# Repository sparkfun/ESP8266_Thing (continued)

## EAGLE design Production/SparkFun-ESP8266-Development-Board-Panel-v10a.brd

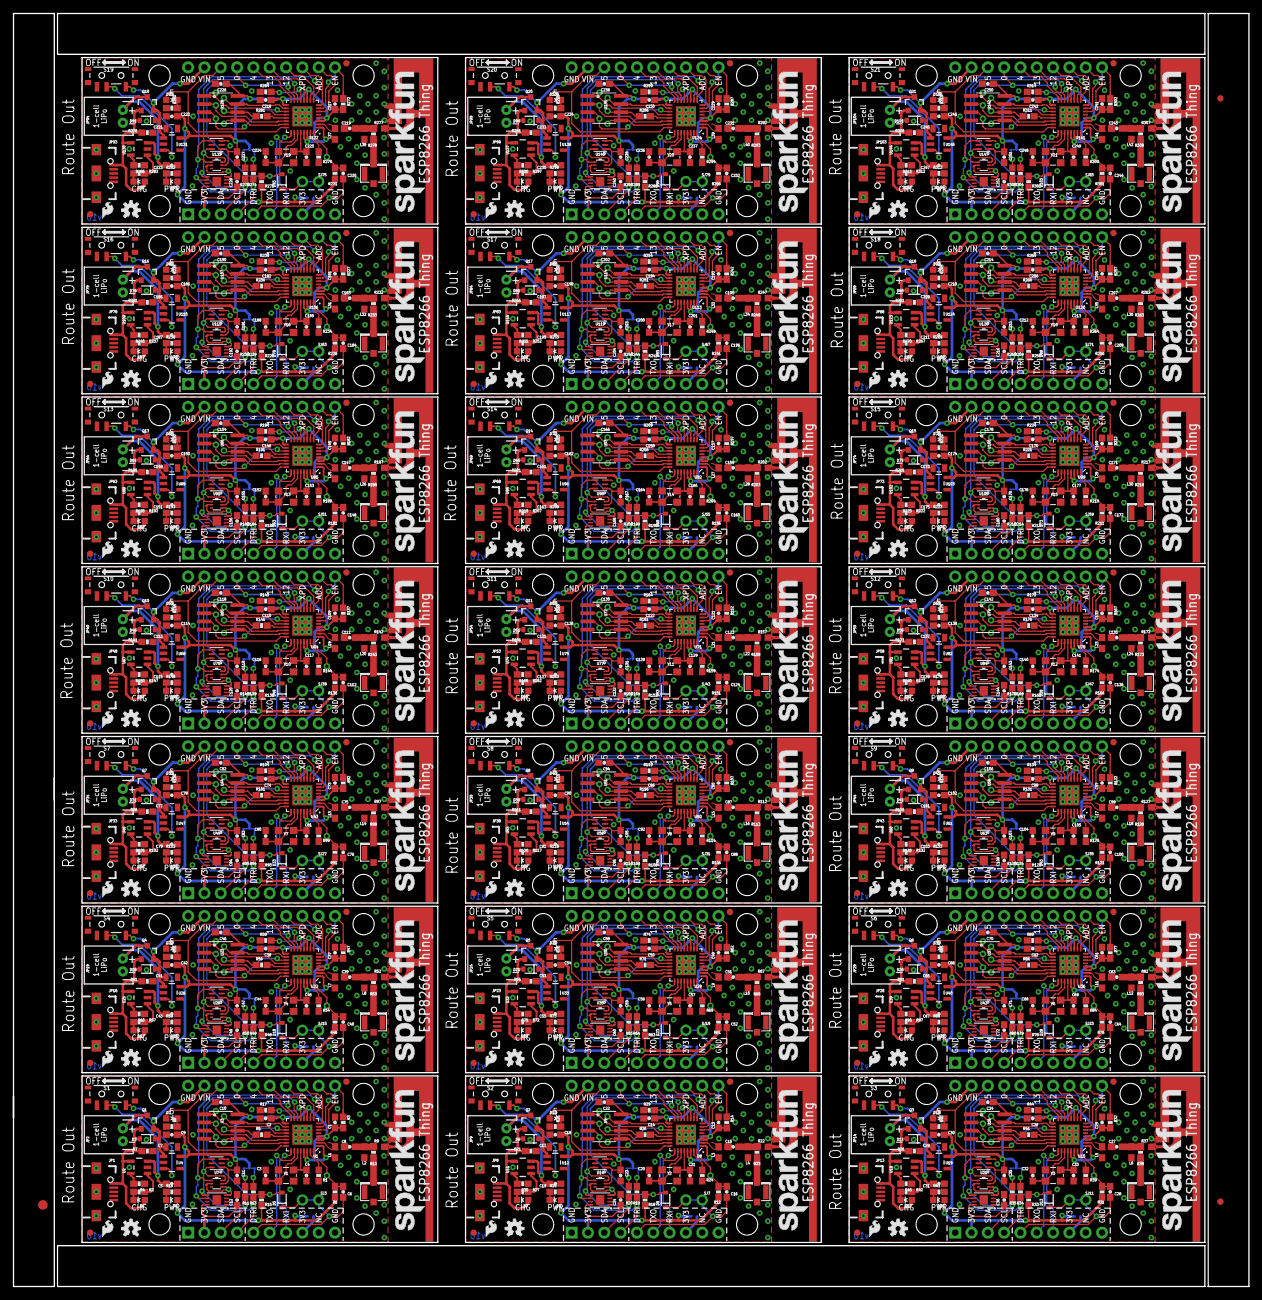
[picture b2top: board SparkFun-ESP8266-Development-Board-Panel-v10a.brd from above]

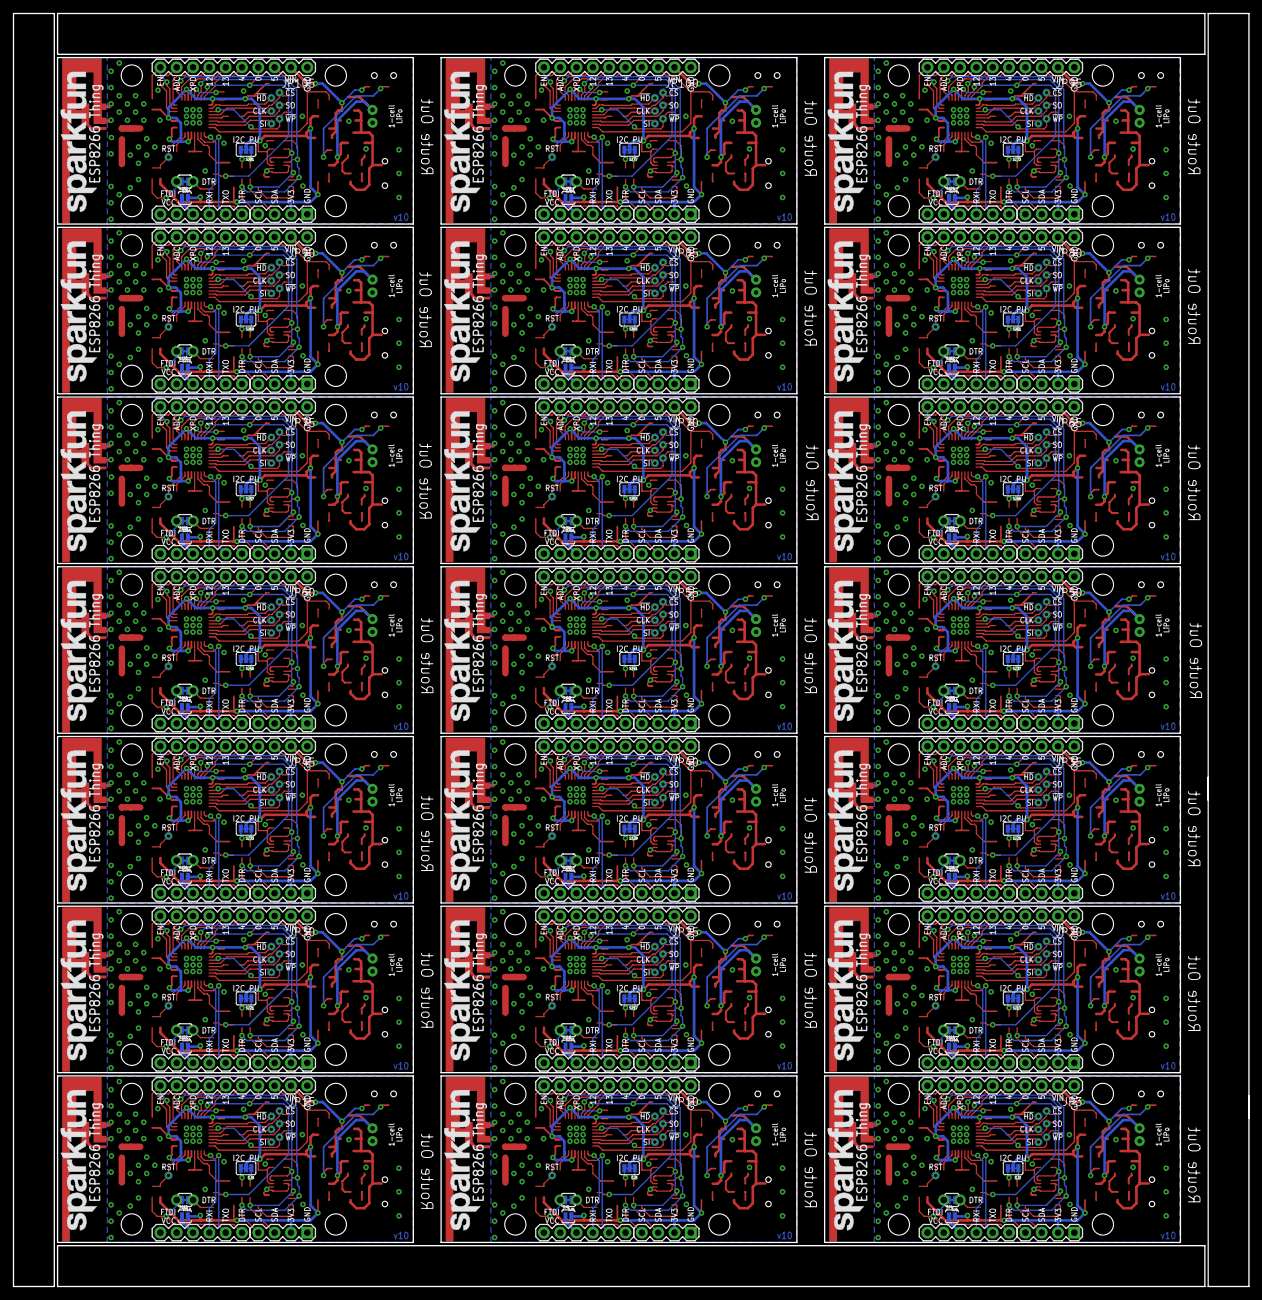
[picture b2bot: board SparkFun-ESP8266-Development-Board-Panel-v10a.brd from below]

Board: 2 copper layers, 192.3 x 198.1 mm, 1515 parts (294 on the bottom side), 924 nets.

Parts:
C1, C13, C25, C37, C49, C61, C73, C85, C97, C109, C121, C133, C145, C157, C169, C181, C193, C205, C217, C229, C241: 10uF; 0603-CAP
C2, C10, C11, C12, C14, C22, C23, C24, C26, C34, C35, C36, C38, C46, C47, C48, C50, C58, C59, C60, C62, C70, C71, C72, C74, C82, C83, C84, C86, C94, C95, C96, C98, C106, C107, C108, C110, C118, C119, C120, C122, C130, C131, C132, C134, C142, C143, C144, C146, C154, C155, C156, C158, C166, C167, C168, C170, C178, C179, C180, C182, C190, C191, C192, C194, C202, C203, C204, C206, C214, C215, C216, C218, C226, C227, C228, C230, C238, C239, C240, C242, C250, C251, C252: 0.1uF; 0603-CAP
C3, C4, C20, C21, C32, C33, C44, C45, C56, C57, C68, C69, C80, C81, C92, C93, C104, C105, C116, C117, C128, C129, C140, C141, C152, C153, C164, C165, C176, C177, C188, C189, C200, C201, C212, C213, C224, C225, C236, C237, C248, C249: 10pF; 0603-CAP
C5, C19, C31, C43, C55, C67, C79, C91, C103, C115, C127, C139, C151, C163, C175, C187, C199, C211, C223, C235, C247: 4.7uF; 0603-CAP
C6, C16, C28, C40, C52, C64, C76, C88, C100, C112, C124, C136, C148, C160, C172, C184, C196, C208, C220, C232, C244: 1.0uF; 0603-CAP
C7, C17, C29, C41, C53, C65, C77, C89, C101, C113, C125, C137, C149, C161, C173, C185, C197, C209, C221, C233, C245: 1.0uF; 0805
C8, C15, C27, C39, C51, C63, C75, C87, C99, C111, C123, C135, C147, C159, C171, C183, C195, C207, C219, C231, C243: 5.6pF; 0603-CAP
C9, C18, C30, C42, C54, C66, C78, C90, C102, C114, C126, C138, C150, C162, C174, C186, C198, C210, C222, C234, C246: 2.2uF; 0603-CAP
D1, D7, D12, D17, D22, D27, D32, D37, D42, D47, D52, D57, D62, D67, D72, D77, D82, D87, D92, D97, D102: YELLOW; LED-0603
D2, D10, D15, D20, D25, D30, D35, D40, D45, D50, D55, D60, D65, D70, D75, D80, D85, D90, D95, D100, D105: GREEN; LED-0603
D3, D6, D11, D16, D21, D26, D31, D36, D41, D46, D51, D56, D61, D66, D71, D76, D81, D86, D91, D96, D101: BAT20J; SOD-323
D4, D9, D14, D19, D24, D29, D34, D39, D44, D49, D54, D59, D64, D69, D74, D79, D84, D89, D94, D99, D104: RED; LED-0603
D5, D8, D13, D18, D23, D28, D33, D38, D43, D48, D53, D58, D63, D68, D73, D78, D83, D88, D93, D98, D103: SOD-323
E1, E2, E3, E4, E5, E6, E7, E8, E9, E10, E11, E12, E13, E14, E15, E16, E17, E18, E19, E20, E21: ANTENNATRACE; TRACE_ANTENNA_2.4GHZ_25.7MM
E$1: FIDUCIAL-1.5X3
E$5, E$6: FIDUCIAL-1X2
FID1, FID2, FID3, FID4, FID5, FID6, FID7, FID8, FID9, FID10, FID11, FID12, FID13, FID14, FID15, FID16, FID17, FID18, FID19, FID20, FID21, FID22, FID23, FID24, FID25, FID26, FID27, FID28, FID29, FID30, FID31, FID32, FID33, FID34, FID35, FID36, FID37, FID38, FID39, FID40, FID41, FID42: FIDUCIAL1X2; FIDUCIAL-1X2
J1, J2, J3, J4, J5, J6, J7, J8, J9, J10, J11, J12, J13, J14, J15, J16, J17, J18, J19, J20, J21: DNP; U.FL
JP1, JP8, JP13, JP18, JP23, JP28, JP33, JP38, JP43, JP48, JP53, JP58, JP63, JP68, JP73, JP78, JP83, JP88, JP93, JP98, JP103: USB; USB-B-MICRO-SMD_V03
JP2, JP9, JP14, JP19, JP24, JP29, JP34, JP39, JP44, JP49, JP54, JP59, JP64, JP69, JP74, JP79, JP84, JP89, JP94, JP99, JP104: LiPo; JST-2-PTH
JP3, JP10, JP15, JP20, JP25, JP30, JP35, JP40, JP45, JP50, JP55, JP60, JP65, JP70, JP75, JP80, JP85, JP90, JP95, JP100, JP105: M10"; 1X10
JP4, JP6, JP11, JP16, JP21, JP26, JP31, JP36, JP41, JP46, JP51, JP56, JP61, JP66, JP71, JP76, JP81, JP86, JP91, JP96, JP101: FTDI_BASICPTH; FTDI_BASIC
JP5, JP7, JP12, JP17, JP22, JP27, JP32, JP37, JP42, JP47, JP52, JP57, JP62, JP67, JP72, JP77, JP82, JP87, JP92, JP97, JP102: I2C; 1X04
L1, L2, L3, L4, L5, L6, L7, L8, L9, L10, L11, L12, L13, L14, L15, L16, L17, L18, L19, L20, L21, L22, L23, L24, L25, L26, L27, L28, L29, L30, L31, L32, L33, L34, L35, L36, L37, L38, L39, L40, L41, L42: DNP; 0603
LOGO1, LOGO2, LOGO5, LOGO8, LOGO9, LOGO12, LOGO13, LOGO16, LOGO17, LOGO20, LOGO21, LOGO24, LOGO25, LOGO28, LOGO29, LOGO32, LOGO33, LOGO36, LOGO37, LOGO40, LOGO41, LOGO44, LOGO45, LOGO48, LOGO49, LOGO52, LOGO53, LOGO56, LOGO57, LOGO60, LOGO61, LOGO64, LOGO65, LOGO68, LOGO69, LOGO72, LOGO73, LOGO76, LOGO77, LOGO80, LOGO81, LOGO84: SFE_LOGO_NAME.2_INCH; SFE_LOGO_NAME_.2
LOGO3, LOGO6, LOGO10, LOGO14, LOGO18, LOGO22, LOGO26, LOGO30, LOGO34, LOGO38, LOGO42, LOGO46, LOGO50, LOGO54, LOGO58, LOGO62, LOGO66, LOGO70, LOGO74, LOGO78, LOGO82: SFE_LOGO_FLAME.1_INCH; SFE_LOGO_FLAME_.1
LOGO4, LOGO7, LOGO11, LOGO15, LOGO19, LOGO23, LOGO27, LOGO31, LOGO35, LOGO39, LOGO43, LOGO47, LOGO51, LOGO55, LOGO59, LOGO63, LOGO67, LOGO71, LOGO75, LOGO79, LOGO83: OSHW-LOGOS; OSHW-LOGO-S
Q1, Q2, Q3, Q4, Q5, Q6, Q7, Q8, Q9, Q10, Q11, Q12, Q13, Q14, Q15, Q16, Q17, Q18, Q19, Q20, Q21: 2.5A/30V; SOT23-3
R1, R24, R39, R54, R69, R84, R99, R114, R129, R144, R159, R174, R189, R204, R219, R234, R249, R264, R279, R294, R309: 12k; 0603-RES
R2, R5, R8, R16, R25, R26, R27, R28, R40, R41, R42, R43, R55, R56, R57, R58, R70, R71, R72, R73, R85, R86, R87, R88, R100, R101, R102, R103, R115, R116, R117, R118, R130, R131, R132, R133, R145, R146, R147, R148, R160, R161, R162, R163, R175, R176, R177, R178, R190, R191, R192, R193, R205, R206, R207, R208, R220, R221, R222, R223, R235, R236, R237, R238, R250, R251, R252, R253, R265, R266, R267, R268, R280, R281, R282, R283, R295, R296, R297, R298, R310, R311, R312, R313: 200; 0603-RES
R3, R6, R7, R12, R14, R17, R21, R29, R31, R32, R36, R44, R46, R47, R51, R59, R61, R62, R66, R74, R76, R77, R81, R89, R91, R92, R96, R104, R106, R107, R111, R119, R121, R122, R126, R134, R136, R137, R141, R149, R151, R152, R156, R164, R166, R167, R171, R179, R181, R182, R186, R194, R196, R197, R201, R209, R211, R212, R216, R224, R226, R227, R231, R239, R241, R242, R246, R254, R256, R257, R261, R269, R271, R272, R276, R284, R286, R287, R291, R299, R301, R302, R306, R314: 10K; 0603-RES
R4, R30, R45, R60, R75, R90, R105, R120, R135, R150, R165, R180, R195, R210, R225, R240, R255, R270, R285, R300, R315: 2.0k; 0603-RES
R9, R22, R37, R52, R67, R82, R97, R112, R127, R142, R157, R172, R187, R202, R217, R232, R247, R262, R277, R292, R307: 0; 0603
R10, R23, R38, R53, R68, R83, R98, R113, R128, R143, R158, R173, R188, R203, R218, R233, R248, R263, R278, R293, R308: DNP; 0603-RES
R11, R13, R19, R20, R34, R35, R49, R50, R64, R65, R79, R80, R94, R95, R109, R110, R124, R125, R139, R140, R154, R155, R169, R170, R184, R185, R199, R200, R214, R215, R229, R230, R244, R245, R259, R260, R274, R275, R289, R290, R304, R305: 2.2k; 0603-RES
R15, R18, R33, R48, R63, R78, R93, R108, R123, R138, R153, R168, R183, R198, R213, R228, R243, R258, R273, R288, R303: 1K; 0603-RES
S1, S2, S3, S4, S5, S6, S7, S8, S9, S10, S11, S12, S13, S14, S15, S16, S17, S18, S19, S20, S21: SWITCH-SPST-SMD-A
SJ1, SJ8, SJ12, SJ16, SJ20, SJ24, SJ28, SJ32, SJ36, SJ40, SJ44, SJ48, SJ52, SJ56, SJ60, SJ64, SJ68, SJ72, SJ76, SJ80, SJ84: PAD-JUMPER-2-NC_BY_TRACE_YES_SILK
SJ2, SJ5, SJ9, SJ13, SJ17, SJ21, SJ25, SJ29, SJ33, SJ37, SJ41, SJ45, SJ49, SJ53, SJ57, SJ61, SJ65, SJ69, SJ73, SJ77, SJ81: PAD-JUMPER-3-3OF3_NC_BY_TRACE_YES_SILK_FULL_BOX
SJ3, SJ7, SJ11, SJ15, SJ19, SJ23, SJ27, SJ31, SJ35, SJ39, SJ43, SJ47, SJ51, SJ55, SJ59, SJ63, SJ67, SJ71, SJ75, SJ79, SJ83: PTH-JUMPER-NC_BOTTOM_NO_SILK
SJ4, SJ6, SJ10, SJ14, SJ18, SJ22, SJ26, SJ30, SJ34, SJ38, SJ42, SJ46, SJ50, SJ54, SJ58, SJ62, SJ66, SJ70, SJ74, SJ78, SJ82: PAD-JUMPER-2-NO_YES_SILK
STANDOFF1, STANDOFF2, STANDOFF3, STANDOFF4, STANDOFF5, STANDOFF6, STANDOFF7, STANDOFF8, STANDOFF9, STANDOFF10, STANDOFF11, STANDOFF12, STANDOFF13, STANDOFF14, STANDOFF15, STANDOFF16, STANDOFF17, STANDOFF18, STANDOFF19, STANDOFF20, STANDOFF21, STANDOFF22, STANDOFF23, STANDOFF24, STANDOFF25, STANDOFF26, STANDOFF27, STANDOFF28, STANDOFF29, STANDOFF30, STANDOFF31, STANDOFF32, STANDOFF33, STANDOFF34, STANDOFF35, STANDOFF36, STANDOFF37, STANDOFF38, STANDOFF39, STANDOFF40, STANDOFF41, STANDOFF42, STANDOFF43, STANDOFF44, STANDOFF45, STANDOFF46, STANDOFF47, STANDOFF48, STANDOFF49, STANDOFF50, STANDOFF51, STANDOFF52, STANDOFF53, STANDOFF54, STANDOFF55, STANDOFF56, STANDOFF57, STANDOFF58, STANDOFF59, STANDOFF60, STANDOFF61, STANDOFF62, STANDOFF63, STANDOFF64, STANDOFF65, STANDOFF66, STANDOFF67, STANDOFF68, STANDOFF69, STANDOFF70, STANDOFF71, STANDOFF72, STANDOFF73, STANDOFF74, STANDOFF75, STANDOFF76, STANDOFF77, STANDOFF78, STANDOFF79, STANDOFF80, STANDOFF81, STANDOFF82, STANDOFF83, STANDOFF84: STAND-OFF
TP1, TP2, TP3, TP4, TP5, TP6, TP7, TP8, TP9, TP10, TP11, TP12, TP13, TP14, TP15, TP16, TP17, TP18, TP19, TP20, TP21, TP22, TP23, TP24, TP25, TP26, TP27, TP28, TP29, TP30, TP31, TP32, TP33, TP34, TP35, TP36, TP37, TP38, TP39, TP40, TP41, TP42, TP43, TP44, TP45, TP46, TP47, TP48, TP49, TP50, TP51, TP52, TP53, TP54, TP55, TP56, TP57, TP58, TP59, TP60, TP61, TP62, TP63, TP64, TP65, TP66, TP67, TP68, TP69, TP70, TP71, TP72, TP73, TP74, TP75, TP76, TP77, TP78, TP79, TP80, TP81, TP82, TP83, TP84, TP85, TP86, TP87, TP88, TP89, TP90, TP91, TP92, TP93, TP94, TP95, TP96, TP97, TP98, TP99, TP100, TP101, TP102, TP103, TP104, TP105, TP106, TP107, TP108, TP109, TP110, TP111, TP112, TP113, TP114, TP115, TP116, TP117, TP118, TP119, TP120, TP121, TP122, TP123, TP124, TP125, TP126, TP127, TP128, TP129, TP130, TP131, TP132, TP133, TP134, TP135, TP136, TP137, TP138, TP139, TP140, TP141, TP142, TP143, TP144, TP145, TP146, TP147: PAD.03X.05
U1, U8, U15, U22, U29, U36, U43, U50, U57, U64, U71, U78, U85, U92, U99, U106, U113, U120, U127, U134, U141: ESP8266; QFN32
U2, U11, U18, U25, U32, U39, U46, U53, U60, U67, U74, U81, U88, U95, U102, U109, U116, U123, U130, U137, U144: MCP73831; SOT23-5
U3, U9, U16, U23, U30, U37, U44, U51, U58, U65, U72, U79, U86, U93, U100, U107, U114, U121, U128, U135, U142: AT25SF041-SOIC8; SO08
U4, U12, U19, U26, U33, U40, U47, U54, U61, U68, U75, U82, U89, U96, U103, U110, U117, U124, U131, U138, U145: AP2112K-3.3V; SOT23-5
U5, U10, U17, U24, U31, U38, U45, U52, U59, U66, U73, U80, U87, U94, U101, U108, U115, U122, U129, U136, U143: ATECC108-MAHDA; UDFN8
U6, U13, U20, U27, U34, U41, U48, U55, U62, U69, U76, U83, U90, U97, U104, U111, U118, U125, U132, U139, U146: TMP1021:1; SOT563-2
U7, U14, U21, U28, U35, U42, U49, U56, U63, U70, U77, U84, U91, U98, U105, U112, U119, U126, U133, U140, U147: TSL2561FN; FN-6
Y1, Y2, Y3, Y4, Y5, Y6, Y7, Y8, Y9, Y10, Y11, Y12, Y13, Y14, Y15, Y16, Y17, Y18, Y19, Y20, Y21: 26MHz; CRYSTAL-SMD-3.2X2.5

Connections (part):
ADC: JP3.9, U1.6
ADC1: JP10.9, U8.6
ADC2: JP15.9, U15.6
ADC3: JP20.9, U22.6
ADC4: JP25.9, U29.6
ADC5: JP30.9, U36.6
ADC6: JP35.9, U43.6
ADC7: JP40.9, U50.6
ADC8: JP45.9, U57.6
ADC9: JP50.9, U64.6
ADC10: JP55.9, U71.6
ADC11: JP60.9, U78.6
ADC12: JP65.9, U85.6
ADC13: JP70.9, U92.6
ADC14: JP75.9, U99.6
ADC15: JP80.9, U106.6
ADC16: JP85.9, U113.6
ADC17: JP90.9, U120.6
ADC18: JP95.9, U127.6
ADC19: JP100.9, U134.6
ADC20: JP105.9, U141.6
ANT: J1.P$3, R10.1
ANT1: J2.P$3, R23.1
ANT2: J3.P$3, R38.1
ANT3: J4.P$3, R53.1
ANT4: J5.P$3, R68.1
ANT5: J6.P$3, R83.1
ANT6: J7.P$3, R98.1
ANT7: J8.P$3, R113.1
ANT8: J9.P$3, R128.1
ANT9: J10.P$3, R143.1
ANT10: J11.P$3, R158.1
ANT11: J12.P$3, R173.1
ANT12: J13.P$3, R188.1
ANT13: J14.P$3, R203.1
ANT14: J15.P$3, R218.1
ANT15: J16.P$3, R233.1
ANT16: J17.P$3, R248.1
ANT17: J18.P$3, R263.1
ANT18: J19.P$3, R278.1
ANT19: J20.P$3, R293.1
ANT20: J21.P$3, R308.1
CHIP_EN: JP3.10, R3.1, U1.7
CHIP_EN1: JP10.10, R14.1, U8.7
CHIP_EN2: JP15.10, R32.1, U15.7
CHIP_EN3: JP20.10, R47.1, U22.7
CHIP_EN4: JP25.10, R62.1, U29.7
CHIP_EN5: JP30.10, R77.1, U36.7
CHIP_EN6: JP35.10, R92.1, U43.7
CHIP_EN7: JP40.10, R107.1, U50.7
CHIP_EN8: JP45.10, R122.1, U57.7
CHIP_EN9: JP50.10, R137.1, U64.7
CHIP_EN10: JP55.10, R152.1, U71.7
CHIP_EN11: JP60.10, R167.1, U78.7
CHIP_EN12: JP65.10, R182.1, U85.7
CHIP_EN13: JP70.10, R197.1, U92.7
CHIP_EN14: JP75.10, R212.1, U99.7
CHIP_EN15: JP80.10, R227.1, U106.7
CHIP_EN16: JP85.10, R242.1, U113.7
CHIP_EN17: JP90.10, R257.1, U120.7
CHIP_EN18: JP95.10, R272.1, U127.7
CHIP_EN19: JP100.10, R287.1, U134.7
CHIP_EN20: JP105.10, R302.1, U141.7
DTR: C6.2, JP4.DTR, SJ1.2, SJ3.1
DTR1: C16.2, JP6.DTR, SJ7.1, SJ8.2
DTR2: C28.2, JP11.DTR, SJ11.1, SJ12.2
DTR3: C40.2, JP16.DTR, SJ15.1, SJ16.2
DTR4: C52.2, JP21.DTR, SJ19.1, SJ20.2
DTR5: C64.2, JP26.DTR, SJ23.1, SJ24.2
DTR6: C76.2, JP31.DTR, SJ27.1, SJ28.2
DTR7: C88.2, JP36.DTR, SJ31.1, SJ32.2
DTR8: C100.2, JP41.DTR, SJ35.1, SJ36.2
DTR9: C112.2, JP46.DTR, SJ39.1, SJ40.2
DTR10: C124.2, JP51.DTR, SJ43.1, SJ44.2
DTR11: C136.2, JP56.DTR, SJ47.1, SJ48.2
DTR12: C148.2, JP61.DTR, SJ51.1, SJ52.2
DTR13: C160.2, JP66.DTR, SJ55.1, SJ56.2
DTR14: C172.2, JP71.DTR, SJ59.1, SJ60.2
DTR15: C184.2, JP76.DTR, SJ63.1, SJ64.2
DTR16: C196.2, JP81.DTR, SJ67.1, SJ68.2
DTR17: C208.2, JP86.DTR, SJ71.1, SJ72.2
DTR18: C220.2, JP91.DTR, SJ75.1, SJ76.2
DTR19: C232.2, JP96.DTR, SJ79.1, SJ80.2
DTR20: C244.2, JP101.DTR, SJ83.1, SJ84.2
FTDI_VCC: JP4.VCC, SJ4.1
FTDI_VCC1: JP6.VCC, SJ6.1
FTDI_VCC2: JP11.VCC, SJ10.1
FTDI_VCC3: JP16.VCC, SJ14.1
FTDI_VCC4: JP21.VCC, SJ18.1
FTDI_VCC5: JP26.VCC, SJ22.1
FTDI_VCC6: JP31.VCC, SJ26.1
FTDI_VCC7: JP36.VCC, SJ30.1
FTDI_VCC8: JP41.VCC, SJ34.1
FTDI_VCC9: JP46.VCC, SJ38.1
FTDI_VCC10: JP51.VCC, SJ42.1
FTDI_VCC11: JP56.VCC, SJ46.1
FTDI_VCC12: JP61.VCC, SJ50.1
FTDI_VCC13: JP66.VCC, SJ54.1
FTDI_VCC14: JP71.VCC, SJ58.1
FTDI_VCC15: JP76.VCC, SJ62.1
FTDI_VCC16: JP81.VCC, SJ66.1
FTDI_VCC17: JP86.VCC, SJ70.1
FTDI_VCC18: JP91.VCC, SJ74.1
FTDI_VCC19: JP96.VCC, SJ78.1
FTDI_VCC20: JP101.VCC, SJ82.1
GND: C1.2, C2.2, C3.1, C4.1, C5.2, C7.2, C9.2, C10.2, C11.2, C12.2, E1.GND, E1.GND2, J1.P$1, J1.P$2, JP1.GND1, JP1.SHIELD1, JP1.SHIELD2, JP1.SHIELD3, JP2.1, JP3.1, JP4.GND, JP5.1, L1.2, L2.2, R1.1, R4.1, R7.1, R8.2, R16.2, R17.1, S1.1, U1.EP, U2.2, U3.4, U4.2, U5.4, U6.2, U6.4, U7.2, U7.3, Y1.2, Y1.4
GND1: C13.2, C14.2, C17.2, C18.2, C19.2, C20.1, C21.1, C22.2, C23.2, C24.2, E2.GND, E2.GND2, J2.P$1, J2.P$2, JP6.GND, JP7.1, JP8.GND1, JP8.SHIELD1, JP8.SHIELD2, JP8.SHIELD3, JP9.1, JP10.1, L3.2, L4.2, R21.1, R24.1, R25.2, R28.2, R29.1, R30.1, S2.1, U8.EP, U9.4, U10.4, U11.2, U12.2, U13.2, U13.4, U14.2, U14.3, Y2.2, Y2.4
GND2: C25.2, C26.2, C29.2, C30.2, C31.2, C32.1, C33.1, C34.2, C35.2, C36.2, E3.GND, E3.GND2, J3.P$1, J3.P$2, JP11.GND, JP12.1, JP13.GND1, JP13.SHIELD1, JP13.SHIELD2, JP13.SHIELD3, JP14.1, JP15.1, L5.2, L6.2, R36.1, R39.1, R40.2, R43.2, R44.1, R45.1, S3.1, U15.EP, U16.4, U17.4, U18.2, U19.2, U20.2, U20.4, U21.2, U21.3, Y3.2, Y3.4
GND3: C37.2, C38.2, C41.2, C42.2, C43.2, C44.1, C45.1, C46.2, C47.2, C48.2, E4.GND, E4.GND2, J4.P$1, J4.P$2, JP16.GND, JP17.1, JP18.GND1, JP18.SHIELD1, JP18.SHIELD2, JP18.SHIELD3, JP19.1, JP20.1, L7.2, L8.2, R51.1, R54.1, R55.2, R58.2, R59.1, R60.1, S4.1, U22.EP, U23.4, U24.4, U25.2, U26.2, U27.2, U27.4, U28.2, U28.3, Y4.2, Y4.4
GND4: C49.2, C50.2, C53.2, C54.2, C55.2, C56.1, C57.1, C58.2, C59.2, C60.2, E5.GND, E5.GND2, J5.P$1, J5.P$2, JP21.GND, JP22.1, JP23.GND1, JP23.SHIELD1, JP23.SHIELD2, JP23.SHIELD3, JP24.1, JP25.1, L9.2, L10.2, R66.1, R69.1, R70.2, R73.2, R74.1, R75.1, S5.1, U29.EP, U30.4, U31.4, U32.2, U33.2, U34.2, U34.4, U35.2, U35.3, Y5.2, Y5.4
GND5: C61.2, C62.2, C65.2, C66.2, C67.2, C68.1, C69.1, C70.2, C71.2, C72.2, E6.GND, E6.GND2, J6.P$1, J6.P$2, JP26.GND, JP27.1, JP28.GND1, JP28.SHIELD1, JP28.SHIELD2, JP28.SHIELD3, JP29.1, JP30.1, L11.2, L12.2, R81.1, R84.1, R85.2, R88.2, R89.1, R90.1, S6.1, U36.EP, U37.4, U38.4, U39.2, U40.2, U41.2, U41.4, U42.2, U42.3, Y6.2, Y6.4
GND6: C73.2, C74.2, C77.2, C78.2, C79.2, C80.1, C81.1, C82.2, C83.2, C84.2, E7.GND, E7.GND2, J7.P$1, J7.P$2, JP31.GND, JP32.1, JP33.GND1, JP33.SHIELD1, JP33.SHIELD2, JP33.SHIELD3, JP34.1, JP35.1, L13.2, L14.2, R96.1, R99.1, R100.2, R103.2, R104.1, R105.1, S7.1, U43.EP, U44.4, U45.4, U46.2, U47.2, U48.2, U48.4, U49.2, U49.3, Y7.2, Y7.4
GND7: C85.2, C86.2, C89.2, C90.2, C91.2, C92.1, C93.1, C94.2, C95.2, C96.2, E8.GND, E8.GND2, J8.P$1, J8.P$2, JP36.GND, JP37.1, JP38.GND1, JP38.SHIELD1, JP38.SHIELD2, JP38.SHIELD3, JP39.1, JP40.1, L15.2, L16.2, R111.1, R114.1, R115.2, R118.2, R119.1, R120.1, S8.1, U50.EP, U51.4, U52.4, U53.2, U54.2, U55.2, U55.4, U56.2, U56.3, Y8.2, Y8.4
GND8: C97.2, C98.2, C101.2, C102.2, C103.2, C104.1, C105.1, C106.2, C107.2, C108.2, E9.GND, E9.GND2, J9.P$1, J9.P$2, JP41.GND, JP42.1, JP43.GND1, JP43.SHIELD1, JP43.SHIELD2, JP43.SHIELD3, JP44.1, JP45.1, L17.2, L18.2, R126.1, R129.1, R130.2, R133.2, R134.1, R135.1, S9.1, U57.EP, U58.4, U59.4, U60.2, U61.2, U62.2, U62.4, U63.2, U63.3, Y9.2, Y9.4
GND9: C109.2, C110.2, C113.2, C114.2, C115.2, C116.1, C117.1, C118.2, C119.2, C120.2, E10.GND, E10.GND2, J10.P$1, J10.P$2, JP46.GND, JP47.1, JP48.GND1, JP48.SHIELD1, JP48.SHIELD2, JP48.SHIELD3, JP49.1, JP50.1, L19.2, L20.2, R141.1, R144.1, R145.2, R148.2, R149.1, R150.1, S10.1, U64.EP, U65.4, U66.4, U67.2, U68.2, U69.2, U69.4, U70.2, U70.3, Y10.2, Y10.4
GND10: C121.2, C122.2, C125.2, C126.2, C127.2, C128.1, C129.1, C130.2, C131.2, C132.2, E11.GND, E11.GND2, J11.P$1, J11.P$2, JP51.GND, JP52.1, JP53.GND1, JP53.SHIELD1, JP53.SHIELD2, JP53.SHIELD3, JP54.1, JP55.1, L21.2, L22.2, R156.1, R159.1, R160.2, R163.2, R164.1, R165.1, S11.1, U71.EP, U72.4, U73.4, U74.2, U75.2, U76.2, U76.4, U77.2, U77.3, Y11.2, Y11.4
GND11: C133.2, C134.2, C137.2, C138.2, C139.2, C140.1, C141.1, C142.2, C143.2, C144.2, E12.GND, E12.GND2, J12.P$1, J12.P$2, JP56.GND, JP57.1, JP58.GND1, JP58.SHIELD1, JP58.SHIELD2, JP58.SHIELD3, JP59.1, JP60.1, L23.2, L24.2, R171.1, R174.1, R175.2, R178.2, R179.1, R180.1, S12.1, U78.EP, U79.4, U80.4, U81.2, U82.2, U83.2, U83.4, U84.2, U84.3, Y12.2, Y12.4
GND12: C145.2, C146.2, C149.2, C150.2, C151.2, C152.1, C153.1, C154.2, C155.2, C156.2, E13.GND, E13.GND2, J13.P$1, J13.P$2, JP61.GND, JP62.1, JP63.GND1, JP63.SHIELD1, JP63.SHIELD2, JP63.SHIELD3, JP64.1, JP65.1, L25.2, L26.2, R186.1, R189.1, R190.2, R193.2, R194.1, R195.1, S13.1, U85.EP, U86.4, U87.4, U88.2, U89.2, U90.2, U90.4, U91.2, U91.3, Y13.2, Y13.4
GND13: C157.2, C158.2, C161.2, C162.2, C163.2, C164.1, C165.1, C166.2, C167.2, C168.2, E14.GND, E14.GND2, J14.P$1, J14.P$2, JP66.GND, JP67.1, JP68.GND1, JP68.SHIELD1, JP68.SHIELD2, JP68.SHIELD3, JP69.1, JP70.1, L27.2, L28.2, R201.1, R204.1, R205.2, R208.2, R209.1, R210.1, S14.1, U92.EP, U93.4, U94.4, U95.2, U96.2, U97.2, U97.4, U98.2, U98.3, Y14.2, Y14.4
GND14: C169.2, C170.2, C173.2, C174.2, C175.2, C176.1, C177.1, C178.2, C179.2, C180.2, E15.GND, E15.GND2, J15.P$1, J15.P$2, JP71.GND, JP72.1, JP73.GND1, JP73.SHIELD1, JP73.SHIELD2, JP73.SHIELD3, JP74.1, JP75.1, L29.2, L30.2, R216.1, R219.1, R220.2, R223.2, R224.1, R225.1, S15.1, U99.EP, U100.4, U101.4, U102.2, U103.2, U104.2, U104.4, U105.2, U105.3, Y15.2, Y15.4
GND15: C181.2, C182.2, C185.2, C186.2, C187.2, C188.1, C189.1, C190.2, C191.2, C192.2, E16.GND, E16.GND2, J16.P$1, J16.P$2, JP76.GND, JP77.1, JP78.GND1, JP78.SHIELD1, JP78.SHIELD2, JP78.SHIELD3, JP79.1, JP80.1, L31.2, L32.2, R231.1, R234.1, R235.2, R238.2, R239.1, R240.1, S16.1, U106.EP, U107.4, U108.4, U109.2, U110.2, U111.2, U111.4, U112.2, U112.3, Y16.2, Y16.4
GND16: C193.2, C194.2, C197.2, C198.2, C199.2, C200.1, C201.1, C202.2, C203.2, C204.2, E17.GND, E17.GND2, J17.P$1, J17.P$2, JP81.GND, JP82.1, JP83.GND1, JP83.SHIELD1, JP83.SHIELD2, JP83.SHIELD3, JP84.1, JP85.1, L33.2, L34.2, R246.1, R249.1, R250.2, R253.2, R254.1, R255.1, S17.1, U113.EP, U114.4, U115.4, U116.2, U117.2, U118.2, U118.4, U119.2, U119.3, Y17.2, Y17.4
GND17: C205.2, C206.2, C209.2, C210.2, C211.2, C212.1, C213.1, C214.2, C215.2, C216.2, E18.GND, E18.GND2, J18.P$1, J18.P$2, JP86.GND, JP87.1, JP88.GND1, JP88.SHIELD1, JP88.SHIELD2, JP88.SHIELD3, JP89.1, JP90.1, L35.2, L36.2, R261.1, R264.1, R265.2, R268.2, R269.1, R270.1, S18.1, U120.EP, U121.4, U122.4, U123.2, U124.2, U125.2, U125.4, U126.2, U126.3, Y18.2, Y18.4
GND18: C217.2, C218.2, C221.2, C222.2, C223.2, C224.1, C225.1, C226.2, C227.2, C228.2, E19.GND, E19.GND2, J19.P$1, J19.P$2, JP91.GND, JP92.1, JP93.GND1, JP93.SHIELD1, JP93.SHIELD2, JP93.SHIELD3, JP94.1, JP95.1, L37.2, L38.2, R276.1, R279.1, R280.2, R283.2, R284.1, R285.1, S19.1, U127.EP, U128.4, U129.4, U130.2, U131.2, U132.2, U132.4, U133.2, U133.3, Y19.2, Y19.4
GND19: C229.2, C230.2, C233.2, C234.2, C235.2, C236.1, C237.1, C238.2, C239.2, C240.2, E20.GND, E20.GND2, J20.P$1, J20.P$2, JP96.GND, JP97.1, JP98.GND1, JP98.SHIELD1, JP98.SHIELD2, JP98.SHIELD3, JP99.1, JP100.1, L39.2, L40.2, R291.1, R294.1, R295.2, R298.2, R299.1, R300.1, S20.1, U134.EP, U135.4, U136.4, U137.2, U138.2, U139.2, U139.4, U140.2, U140.3, Y20.2, Y20.4
GND20: C241.2, C242.2, C245.2, C246.2, C247.2, C248.1, C249.1, C250.2, C251.2, C252.2, E21.GND, E21.GND2, J21.P$1, J21.P$2, JP101.GND, JP102.1, JP103.GND1, JP103.SHIELD1, JP103.SHIELD2, JP103.SHIELD3, JP104.1, JP105.1, L41.2, L42.2, R306.1, R309.1, R310.2, R313.2, R314.1, R315.1, S21.1, U141.EP, U142.4, U143.4, U144.2, U145.2, U146.2, U146.4, U147.2, U147.3, Y21.2, Y21.4
GPIO0: D5.A, JP3.4, R15.1, U1.15
GPIO1: D8.A, JP10.4, R18.1, U8.15
GPIO2: D10.A, JP10.3, U8.24
GPIO2/SDA: JP5.3, R11.1, U1.14, U5.5, U6.6, U7.6
GPIO2/SDA1: JP7.3, R20.1, U8.14, U10.5, U13.6, U14.6
GPIO2/SDA2: JP12.3, R35.1, U15.14, U17.5, U20.6, U21.6
GPIO2/SDA3: JP17.3, R50.1, U22.14, U24.5, U27.6, U28.6
GPIO2/SDA4: JP22.3, R65.1, U29.14, U31.5, U34.6, U35.6
GPIO2/SDA5: JP27.3, R80.1, U36.14, U38.5, U41.6, U42.6
GPIO2/SDA6: JP32.3, R95.1, U43.14, U45.5, U48.6, U49.6
GPIO2/SDA7: JP37.3, R110.1, U50.14, U52.5, U55.6, U56.6
GPIO2/SDA8: JP42.3, R125.1, U57.14, U59.5, U62.6, U63.6
GPIO2/SDA9: JP47.3, R140.1, U64.14, U66.5, U69.6, U70.6
GPIO2/SDA10: JP52.3, R155.1, U71.14, U73.5, U76.6, U77.6
GPIO2/SDA11: JP57.3, R170.1, U78.14, U80.5, U83.6, U84.6
GPIO2/SDA12: JP62.3, R185.1, U85.14, U87.5, U90.6, U91.6
GPIO2/SDA13: JP67.3, R200.1, U92.14, U94.5, U97.6, U98.6
GPIO2/SDA14: JP72.3, R215.1, U99.14, U101.5, U104.6, U105.6
GPIO2/SDA15: JP77.3, R230.1, U106.14, U108.5, U111.6, U112.6
GPIO2/SDA16: JP82.3, R245.1, U113.14, U115.5, U118.6, U119.6
GPIO2/SDA17: JP87.3, R260.1, U120.14, U122.5, U125.6, U126.6
GPIO2/SDA18: JP92.3, R275.1, U127.14, U129.5, U132.6, U133.6
GPIO2/SDA19: JP97.3, R290.1, U134.14, U136.5, U139.6, U140.6
GPIO2/SDA20: JP102.3, R305.1, U141.14, U143.5, U146.6, U147.6
GPIO3: JP10.5, U8.16
GPIO4: JP3.5, U1.16
GPIO5: D2.A, JP3.3, U1.24
GPIO6: JP10.8, U8.8
GPIO7: R29.2, U8.13
GPIO8: JP10.6, U8.12
GPIO9: JP10.7, U8.10
GPIO10: D13.A, JP15.4, R33.1, U15.15
GPIO11: D15.A, JP15.3, U15.24
GPIO12: JP3.7, U1.10
GPIO13: JP3.6, U1.12
GPIO14: JP15.5, U15.16
GPIO14/SCL: JP5.4, R13.1, U1.9, U5.6, U6.1, U7.4
GPIO14/SCL1: JP7.4, R19.1, U8.9, U10.6, U13.1, U14.4
GPIO14/SCL2: JP12.4, R34.1, U15.9, U17.6, U20.1, U21.4
GPIO14/SCL3: JP17.4, R49.1, U22.9, U24.6, U27.1, U28.4
GPIO14/SCL4: JP22.4, R64.1, U29.9, U31.6, U34.1, U35.4
GPIO14/SCL5: JP27.4, R79.1, U36.9, U38.6, U41.1, U42.4
GPIO14/SCL6: JP32.4, R94.1, U43.9, U45.6, U48.1, U49.4
GPIO14/SCL7: JP37.4, R109.1, U50.9, U52.6, U55.1, U56.4
GPIO14/SCL8: JP42.4, R124.1, U57.9, U59.6, U62.1, U63.4
GPIO14/SCL9: JP47.4, R139.1, U64.9, U66.6, U69.1, U70.4
GPIO14/SCL10: JP52.4, R154.1, U71.9, U73.6, U76.1, U77.4
GPIO14/SCL11: JP57.4, R169.1, U78.9, U80.6, U83.1, U84.4
GPIO14/SCL12: JP62.4, R184.1, U85.9, U87.6, U90.1, U91.4
GPIO14/SCL13: JP67.4, R199.1, U92.9, U94.6, U97.1, U98.4
GPIO14/SCL14: JP72.4, R214.1, U99.9, U101.6, U104.1, U105.4
GPIO14/SCL15: JP77.4, R229.1, U106.9, U108.6, U111.1, U112.4
GPIO14/SCL16: JP82.4, R244.1, U113.9, U115.6, U118.1, U119.4
GPIO14/SCL17: JP87.4, R259.1, U120.9, U122.6, U125.1, U126.4
GPIO14/SCL18: JP92.4, R274.1, U127.9, U129.6, U132.1, U133.4
GPIO14/SCL19: JP97.4, R289.1, U134.9, U136.6, U139.1, U140.4
GPIO14/SCL20: JP102.4, R304.1, U141.9, U143.6, U146.1, U147.4
GPIO15: R17.2, U1.13
GPIO16: JP3.8, U1.8
GPIO17: JP15.8, U15.8
GPIO18: R44.2, U15.13
GPIO19: JP15.6, U15.12
GPIO20: JP15.7, U15.10
GPIO21: D18.A, JP20.4, R48.1, U22.15
GPIO22: D20.A, JP20.3, U22.24
GPIO23: JP20.5, U22.16
GPIO24: JP20.8, U22.8
GPIO25: R59.2, U22.13
GPIO26: JP20.6, U22.12
GPIO27: JP20.7, U22.10
GPIO28: D23.A, JP25.4, R63.1, U29.15
GPIO29: D25.A, JP25.3, U29.24
GPIO30: JP25.5, U29.16
GPIO31: JP25.8, U29.8
GPIO32: R74.2, U29.13
GPIO33: JP25.6, U29.12
GPIO34: JP25.7, U29.10
GPIO35: D28.A, JP30.4, R78.1, U36.15
GPIO36: D30.A, JP30.3, U36.24
GPIO37: JP30.5, U36.16
GPIO38: JP30.8, U36.8
GPIO39: R89.2, U36.13
GPIO40: JP30.6, U36.12
GPIO41: JP30.7, U36.10
GPIO42: D33.A, JP35.4, R93.1, U43.15
GPIO43: D35.A, JP35.3, U43.24
GPIO44: JP35.5, U43.16
GPIO45: JP35.8, U43.8
GPIO46: R104.2, U43.13
GPIO47: JP35.6, U43.12
GPIO48: JP35.7, U43.10
GPIO49: D38.A, JP40.4, R108.1, U50.15
GPIO50: D40.A, JP40.3, U50.24
GPIO51: JP40.5, U50.16
GPIO52: JP40.8, U50.8
GPIO53: R119.2, U50.13
GPIO54: JP40.6, U50.12
GPIO55: JP40.7, U50.10
GPIO56: D43.A, JP45.4, R123.1, U57.15
GPIO57: D45.A, JP45.3, U57.24
GPIO58: JP45.5, U57.16
GPIO59: JP45.8, U57.8
GPIO60: R134.2, U57.13
GPIO61: JP45.6, U57.12
GPIO62: JP45.7, U57.10
GPIO63: D48.A, JP50.4, R138.1, U64.15
GPIO64: D50.A, JP50.3, U64.24
GPIO65: JP50.5, U64.16
GPIO66: JP50.8, U64.8
GPIO67: R149.2, U64.13
GPIO68: JP50.6, U64.12
GPIO69: JP50.7, U64.10
GPIO70: D53.A, JP55.4, R153.1, U71.15
GPIO71: D55.A, JP55.3, U71.24
GPIO72: JP55.5, U71.16
GPIO73: JP55.8, U71.8
GPIO74: R164.2, U71.13
GPIO75: JP55.6, U71.12
GPIO76: JP55.7, U71.10
GPIO77: D58.A, JP60.4, R168.1, U78.15
GPIO78: D60.A, JP60.3, U78.24
GPIO79: JP60.5, U78.16
GPIO80: JP60.8, U78.8
GPIO81: R179.2, U78.13
GPIO82: JP60.6, U78.12
GPIO83: JP60.7, U78.10
GPIO84: D63.A, JP65.4, R183.1, U85.15
GPIO85: D65.A, JP65.3, U85.24
GPIO86: JP65.5, U85.16
GPIO87: JP65.8, U85.8
GPIO88: R194.2, U85.13
GPIO89: JP65.6, U85.12
GPIO90: JP65.7, U85.10
GPIO91: D68.A, JP70.4, R198.1, U92.15
GPIO92: D70.A, JP70.3, U92.24
GPIO93: JP70.5, U92.16
GPIO94: JP70.8, U92.8
GPIO95: R209.2, U92.13
GPIO96: JP70.6, U92.12
GPIO97: JP70.7, U92.10
GPIO98: D73.A, JP75.4, R213.1, U99.15
GPIO99: D75.A, JP75.3, U99.24
GPIO100: JP75.5, U99.16
GPIO101: JP75.8, U99.8
GPIO102: R224.2, U99.13
GPIO103: JP75.6, U99.12
GPIO104: JP75.7, U99.10
GPIO105: D78.A, JP80.4, R228.1, U106.15
GPIO106: D80.A, JP80.3, U106.24
GPIO107: JP80.5, U106.16
GPIO108: JP80.8, U106.8
GPIO109: R239.2, U106.13
GPIO110: JP80.6, U106.12
GPIO111: JP80.7, U106.10
GPIO112: D83.A, JP85.4, R243.1, U113.15
GPIO113: D85.A, JP85.3, U113.24
GPIO114: JP85.5, U113.16
GPIO115: JP85.8, U113.8
GPIO116: R254.2, U113.13
GPIO117: JP85.6, U113.12
GPIO118: JP85.7, U113.10
GPIO119: D88.A, JP90.4, R258.1, U120.15
GPIO120: D90.A, JP90.3, U120.24
GPIO121: JP90.5, U120.16
GPIO122: JP90.8, U120.8
GPIO123: R269.2, U120.13
GPIO124: JP90.6, U120.12
GPIO125: JP90.7, U120.10
GPIO126: D93.A, JP95.4, R273.1, U127.15
GPIO127: D95.A, JP95.3, U127.24
GPIO128: JP95.5, U127.16
GPIO129: JP95.8, U127.8
GPIO130: R284.2, U127.13
GPIO131: JP95.6, U127.12
GPIO132: JP95.7, U127.10
GPIO133: D98.A, JP100.4, R288.1, U134.15
GPIO134: D100.A, JP100.3, U134.24
GPIO135: JP100.5, U134.16
GPIO136: JP100.8, U134.8
GPIO137: R299.2, U134.13
GPIO138: JP100.6, U134.12
GPIO139: JP100.7, U134.10
GPIO140: D103.A, JP105.4, R303.1, U141.15
GPIO141: D105.A, JP105.3, U141.24
GPIO142: JP105.5, U141.16
GPIO143: JP105.8, U141.8
GPIO144: R314.2, U141.13
GPIO145: JP105.6, U141.12
GPIO146: JP105.7, U141.10
LNA: C8.1, L1.1, U1.2
LNA1: C15.1, L3.1, U8.2
LNA2: C27.1, L5.1, U15.2
LNA3: C39.1, L7.1, U22.2
LNA4: C51.1, L9.1, U29.2
LNA5: C63.1, L11.1, U36.2
LNA6: C75.1, L13.1, U43.2
LNA7: C87.1, L15.1, U50.2
LNA8: C99.1, L17.1, U57.2
LNA9: C111.1, L19.1, U64.2
LNA10: C123.1, L21.1, U71.2
LNA11: C135.1, L23.1, U78.2
LNA12: C147.1, L25.1, U85.2
LNA13: C159.1, L27.1, U92.2
LNA14: C171.1, L29.1, U99.2
LNA15: C183.1, L31.1, U106.2
LNA16: C195.1, L33.1, U113.2
LNA17: C207.1, L35.1, U120.2
LNA18: C219.1, L37.1, U127.2
LNA19: C231.1, L39.1, U134.2
LNA20: C243.1, L41.1, U141.2
unnamed: R1.2, U1.31
unnamed: C4.2, U1.28, Y1.3
unnamed: C3.2, U1.27, Y1.1
unnamed: D4.C, R16.1
unnamed: C8.2, L2.1, R9.2, R10.2
unnamed: R5.2, U1.21
unnamed: D5.C, SJ1.1, SJ3.2
unnamed: R24.2, U8.31
unnamed: R11.2, SJ2.1
unnamed: R13.2, SJ2.3
unnamed: S1.2, U4.3
unnamed: C21.2, U8.28, Y2.3
unnamed: C20.2, U8.27, Y2.1
unnamed: R4.2, U2.5
unnamed: D2.C, R8.1
unnamed: C15.2, L4.1, R22.2, R23.2
unnamed: D1.C, R2.2
unnamed: R2.1, U2.1
unnamed: D7.C, R27.2
unnamed: R27.1, U11.1
unnamed: R30.2, U11.5
unnamed: R26.2, U8.21
unnamed: R20.2, SJ5.1
unnamed: R19.2, SJ5.3
unnamed: D10.C, R25.1
unnamed: D9.C, R28.1
unnamed: D8.C, SJ7.2, SJ8.1
unnamed: S2.2, U12.3
unnamed: R39.2, U15.31
unnamed: C33.2, U15.28, Y3.3
unnamed: C32.2, U15.27, Y3.1
unnamed: C27.2, L6.1, R37.2, R38.2
unnamed: D12.C, R42.2
unnamed: R42.1, U18.1
unnamed: R45.2, U18.5
unnamed: R41.2, U15.21
unnamed: R35.2, SJ9.1
unnamed: R34.2, SJ9.3
unnamed: D15.C, R40.1
unnamed: D14.C, R43.1
unnamed: D13.C, SJ11.2, SJ12.1
unnamed: S3.2, U19.3
unnamed: R54.2, U22.31
unnamed: C45.2, U22.28, Y4.3
unnamed: C44.2, U22.27, Y4.1
unnamed: C39.2, L8.1, R52.2, R53.2
unnamed: D17.C, R57.2
unnamed: R57.1, U25.1
unnamed: R60.2, U25.5
unnamed: R56.2, U22.21
unnamed: R50.2, SJ13.1
unnamed: R49.2, SJ13.3
unnamed: D20.C, R55.1
unnamed: D19.C, R58.1
unnamed: D18.C, SJ15.2, SJ16.1
unnamed: S4.2, U26.3
unnamed: R69.2, U29.31
unnamed: C57.2, U29.28, Y5.3
unnamed: C56.2, U29.27, Y5.1
unnamed: C51.2, L10.1, R67.2, R68.2
unnamed: D22.C, R72.2
unnamed: R72.1, U32.1
unnamed: R75.2, U32.5
unnamed: R71.2, U29.21
unnamed: R65.2, SJ17.1
unnamed: R64.2, SJ17.3
unnamed: D25.C, R70.1
unnamed: D24.C, R73.1
unnamed: D23.C, SJ19.2, SJ20.1
unnamed: S5.2, U33.3
unnamed: R84.2, U36.31
unnamed: C69.2, U36.28, Y6.3
unnamed: C68.2, U36.27, Y6.1
unnamed: C63.2, L12.1, R82.2, R83.2
unnamed: D27.C, R87.2
unnamed: R87.1, U39.1
unnamed: R90.2, U39.5
unnamed: R86.2, U36.21
unnamed: R80.2, SJ21.1
unnamed: R79.2, SJ21.3
unnamed: D30.C, R85.1
unnamed: D29.C, R88.1
unnamed: D28.C, SJ23.2, SJ24.1
unnamed: S6.2, U40.3
unnamed: R99.2, U43.31
unnamed: C81.2, U43.28, Y7.3
unnamed: C80.2, U43.27, Y7.1
unnamed: C75.2, L14.1, R97.2, R98.2
unnamed: D32.C, R102.2
unnamed: R102.1, U46.1
unnamed: R105.2, U46.5
unnamed: R101.2, U43.21
unnamed: R95.2, SJ25.1
unnamed: R94.2, SJ25.3
unnamed: D35.C, R100.1
unnamed: D34.C, R103.1
unnamed: D33.C, SJ27.2, SJ28.1
unnamed: S7.2, U47.3
unnamed: R114.2, U50.31
unnamed: C93.2, U50.28, Y8.3
unnamed: C92.2, U50.27, Y8.1
unnamed: C87.2, L16.1, R112.2, R113.2
unnamed: D37.C, R117.2
unnamed: R117.1, U53.1
unnamed: R120.2, U53.5
unnamed: R116.2, U50.21
unnamed: R110.2, SJ29.1
unnamed: R109.2, SJ29.3
unnamed: D40.C, R115.1
unnamed: D39.C, R118.1
unnamed: D38.C, SJ31.2, SJ32.1
unnamed: S8.2, U54.3
unnamed: R129.2, U57.31
unnamed: C105.2, U57.28, Y9.3
unnamed: C104.2, U57.27, Y9.1
unnamed: C99.2, L18.1, R127.2, R128.2
unnamed: D42.C, R132.2
unnamed: R132.1, U60.1
unnamed: R135.2, U60.5
unnamed: R131.2, U57.21
unnamed: R125.2, SJ33.1
unnamed: R124.2, SJ33.3
unnamed: D45.C, R130.1
unnamed: D44.C, R133.1
unnamed: D43.C, SJ35.2, SJ36.1
unnamed: S9.2, U61.3
unnamed: R144.2, U64.31
unnamed: C117.2, U64.28, Y10.3
unnamed: C116.2, U64.27, Y10.1
unnamed: C111.2, L20.1, R142.2, R143.2
unnamed: D47.C, R147.2
unnamed: R147.1, U67.1
unnamed: R150.2, U67.5
unnamed: R146.2, U64.21
unnamed: R140.2, SJ37.1
unnamed: R139.2, SJ37.3
unnamed: D50.C, R145.1
unnamed: D49.C, R148.1
unnamed: D48.C, SJ39.2, SJ40.1
unnamed: S10.2, U68.3
unnamed: R159.2, U71.31
unnamed: C129.2, U71.28, Y11.3
unnamed: C128.2, U71.27, Y11.1
unnamed: C123.2, L22.1, R157.2, R158.2
unnamed: D52.C, R162.2
unnamed: R162.1, U74.1
unnamed: R165.2, U74.5
unnamed: R161.2, U71.21
unnamed: R155.2, SJ41.1
unnamed: R154.2, SJ41.3
unnamed: D55.C, R160.1
unnamed: D54.C, R163.1
unnamed: D53.C, SJ43.2, SJ44.1
unnamed: S11.2, U75.3
unnamed: R174.2, U78.31
unnamed: C141.2, U78.28, Y12.3
unnamed: C140.2, U78.27, Y12.1
unnamed: C135.2, L24.1, R172.2, R173.2
unnamed: D57.C, R177.2
unnamed: R177.1, U81.1
unnamed: R180.2, U81.5
unnamed: R176.2, U78.21
unnamed: R170.2, SJ45.1
unnamed: R169.2, SJ45.3
unnamed: D60.C, R175.1
unnamed: D59.C, R178.1
unnamed: D58.C, SJ47.2, SJ48.1
unnamed: S12.2, U82.3
unnamed: R189.2, U85.31
unnamed: C153.2, U85.28, Y13.3
unnamed: C152.2, U85.27, Y13.1
unnamed: C147.2, L26.1, R187.2, R188.2
unnamed: D62.C, R192.2
unnamed: R192.1, U88.1
unnamed: R195.2, U88.5
unnamed: R191.2, U85.21
unnamed: R185.2, SJ49.1
unnamed: R184.2, SJ49.3
unnamed: D65.C, R190.1
unnamed: D64.C, R193.1
unnamed: D63.C, SJ51.2, SJ52.1
unnamed: S13.2, U89.3
unnamed: R204.2, U92.31
unnamed: C165.2, U92.28, Y14.3
unnamed: C164.2, U92.27, Y14.1
unnamed: C159.2, L28.1, R202.2, R203.2
unnamed: D67.C, R207.2
unnamed: R207.1, U95.1
unnamed: R210.2, U95.5
unnamed: R206.2, U92.21
unnamed: R200.2, SJ53.1
unnamed: R199.2, SJ53.3
unnamed: D70.C, R205.1
unnamed: D69.C, R208.1
unnamed: D68.C, SJ55.2, SJ56.1
unnamed: S14.2, U96.3
unnamed: R219.2, U99.31
unnamed: C177.2, U99.28, Y15.3
unnamed: C176.2, U99.27, Y15.1
unnamed: C171.2, L30.1, R217.2, R218.2
unnamed: D72.C, R222.2
unnamed: R222.1, U102.1
unnamed: R225.2, U102.5
unnamed: R221.2, U99.21
unnamed: R215.2, SJ57.1
unnamed: R214.2, SJ57.3
unnamed: D75.C, R220.1
unnamed: D74.C, R223.1
unnamed: D73.C, SJ59.2, SJ60.1
unnamed: S15.2, U103.3
unnamed: R234.2, U106.31
unnamed: C189.2, U106.28, Y16.3
unnamed: C188.2, U106.27, Y16.1
unnamed: C183.2, L32.1, R232.2, R233.2
unnamed: D77.C, R237.2
unnamed: R237.1, U109.1
unnamed: R240.2, U109.5
unnamed: R236.2, U106.21
unnamed: R230.2, SJ61.1
unnamed: R229.2, SJ61.3
unnamed: D80.C, R235.1
unnamed: D79.C, R238.1
unnamed: D78.C, SJ63.2, SJ64.1
unnamed: S16.2, U110.3
unnamed: R249.2, U113.31
unnamed: C201.2, U113.28, Y17.3
unnamed: C200.2, U113.27, Y17.1
unnamed: C195.2, L34.1, R247.2, R248.2
unnamed: D82.C, R252.2
unnamed: R252.1, U116.1
unnamed: R255.2, U116.5
unnamed: R251.2, U113.21
unnamed: R245.2, SJ65.1
unnamed: R244.2, SJ65.3
unnamed: D85.C, R250.1
unnamed: D84.C, R253.1
unnamed: D83.C, SJ67.2, SJ68.1
unnamed: S17.2, U117.3
unnamed: R264.2, U120.31
unnamed: C213.2, U120.28, Y18.3
unnamed: C212.2, U120.27, Y18.1
unnamed: C207.2, L36.1, R262.2, R263.2
unnamed: D87.C, R267.2
unnamed: R267.1, U123.1
unnamed: R270.2, U123.5
unnamed: R266.2, U120.21
unnamed: R260.2, SJ69.1
unnamed: R259.2, SJ69.3
unnamed: D90.C, R265.1
unnamed: D89.C, R268.1
unnamed: D88.C, SJ71.2, SJ72.1
unnamed: S18.2, U124.3
unnamed: R279.2, U127.31
unnamed: C225.2, U127.28, Y19.3
unnamed: C224.2, U127.27, Y19.1
unnamed: C219.2, L38.1, R277.2, R278.2
unnamed: D92.C, R282.2
unnamed: R282.1, U130.1
unnamed: R285.2, U130.5
unnamed: R281.2, U127.21
unnamed: R275.2, SJ73.1
unnamed: R274.2, SJ73.3
unnamed: D95.C, R280.1
unnamed: D94.C, R283.1
unnamed: D93.C, SJ75.2, SJ76.1
unnamed: S19.2, U131.3
unnamed: R294.2, U134.31
unnamed: C237.2, U134.28, Y20.3
unnamed: C236.2, U134.27, Y20.1
unnamed: C231.2, L40.1, R292.2, R293.2
unnamed: D97.C, R297.2
unnamed: R297.1, U137.1
unnamed: R300.2, U137.5
unnamed: R296.2, U134.21
unnamed: R290.2, SJ77.1
unnamed: R289.2, SJ77.3
unnamed: D100.C, R295.1
unnamed: D99.C, R298.1
unnamed: D98.C, SJ79.2, SJ80.1
unnamed: S20.2, U138.3
unnamed: R309.2, U141.31
unnamed: C249.2, U141.28, Y21.3
unnamed: C248.2, U141.27, Y21.1
unnamed: C243.2, L42.1, R307.2, R308.2
unnamed: D102.C, R312.2
unnamed: R312.1, U144.1
unnamed: R315.2, U144.5
unnamed: R311.2, U141.21
unnamed: R305.2, SJ81.1
unnamed: R304.2, SJ81.3
unnamed: D105.C, R310.1
unnamed: D104.C, R313.1
unnamed: D103.C, SJ83.2, SJ84.1
unnamed: S21.2, U145.3
RESET: C6.1, R6.1, TP7.P$1, U1.32
RESET1: C16.1, R12.1, TP8.P$1, U8.32
RESET2: C28.1, R31.1, TP15.P$1, U15.32
RESET3: C40.1, R46.1, TP22.P$1, U22.32
RESET4: C52.1, R61.1, TP29.P$1, U29.32
RESET5: C64.1, R76.1, TP36.P$1, U36.32
RESET6: C76.1, R91.1, TP43.P$1, U43.32
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
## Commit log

2014-11-19 Initial hardware commit
2014-11-19 Adding temporary library. Includes trace antenna(s) and ATECC108.
2014-11-20 Straightening out some nets coming out of ESP8266. Value JP5. Flag label on RESET.
2014-11-20 Adding power LED. Re-arranging power circuitry. Breaking out pin 5.
2014-11-20 Fixing net names for flash signals. Updating bottom silk labels
2015-01-18 Adding pull-down resistor to GPIO15 (required to upload). Not broken out any more.
2015-01-19 Re-arranging 10-pin header pin-out.
2015-01-21 Adding light and temperature sensors. Adding ON/OFF switch. Simplifying DTR-GPIO0 circuit.
2015-01-21 Swapping colors of PWR and pin 5 LEDs. Adding SMD jumper to GPIO0/DTR.
2015-02-23 Revising silkscreen. Optimizing some traces. Updated to v10.
2015-02-26 Removing silk labels on sensors. Changing R4 to 2k (charge at 500mA).
2015-03-02 Adding PROD_ID to U1, S1, and Y1.
2015-03-03 Extending border dimension out to grid.
2015-03-03 Updating dimensions measure to 2.2in.
2015-03-03 Bringing board width down to 2.18 inches.
2015-03-04 created panel v10
2015-03-06 Revising TMP102, ATECC108 & TSL2561 to DNP. Moving dimensions to correct layer.
2015-03-06 Renaming eagle files to SparkFun_ESP8266_Thing.
2015-05-21 Fixing flash size information in schematic.
2015-05-22 Mapping new parts to equivalent devices in the SparkFun libraries.
2015-09-22 Updating directory name for consistency
2015-09-22 Adding graphical datasheets
2015-09-22 Removing checklist, adding .git files, adding license file
2016-01-21 Added documentation to README
2016-01-22 Added PDF board and schematic
2018-09-28 Remove Phant Silkscreen
    - Remove Phant and data.sparkfun.com silkscreen on .brd files in hardware and production folder.
    - Update file names
2019-04-22 Fix Silkscreen and Copper Width 0 Issue
    - Replace Silkscreen for SparkFun, SFE Flame, OSH logo, and RF antenna on individual board and panel with current packages from the SparkFun Eagle Library. By having a defined width for the silkscree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
